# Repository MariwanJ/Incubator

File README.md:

# Incubator Using PID controller - Arduino Nano.

The incubator system is built using an Arduino Nano and a PID controller. The key components include:

- Incubator enclosure
- PID controller for temperature regulation
- Arduino Nano as the main microcontroller
- Egg turner mechanism for gently rotating the eggs during incubation

The egg turner is an essential part of the incubator system, as it helps ensure the eggs develop properly by exposing different areas to the heat and humidity within the incubator. 

Note that the specific 3D printed holder or design for the egg turner is not included, as there are many different options and choices available for this component.

An additional Arduino board is used to control the egg turner mechanism separately from the main incubator controller.

Feel free to modify, improve, and submit pull requests to the GitHub repository for this project.

Additional Notes:

- This incubator project was originally developed in 2020.

- The photos included show an earlier, faulty version of the incubator. These were added to demonstrate the issues that were targeted and fixed in the updated design.

- The design has been further updated to fix other issues and add more footprints, using KICAD 7.0.

Mariwan Jalal 2023-05-13

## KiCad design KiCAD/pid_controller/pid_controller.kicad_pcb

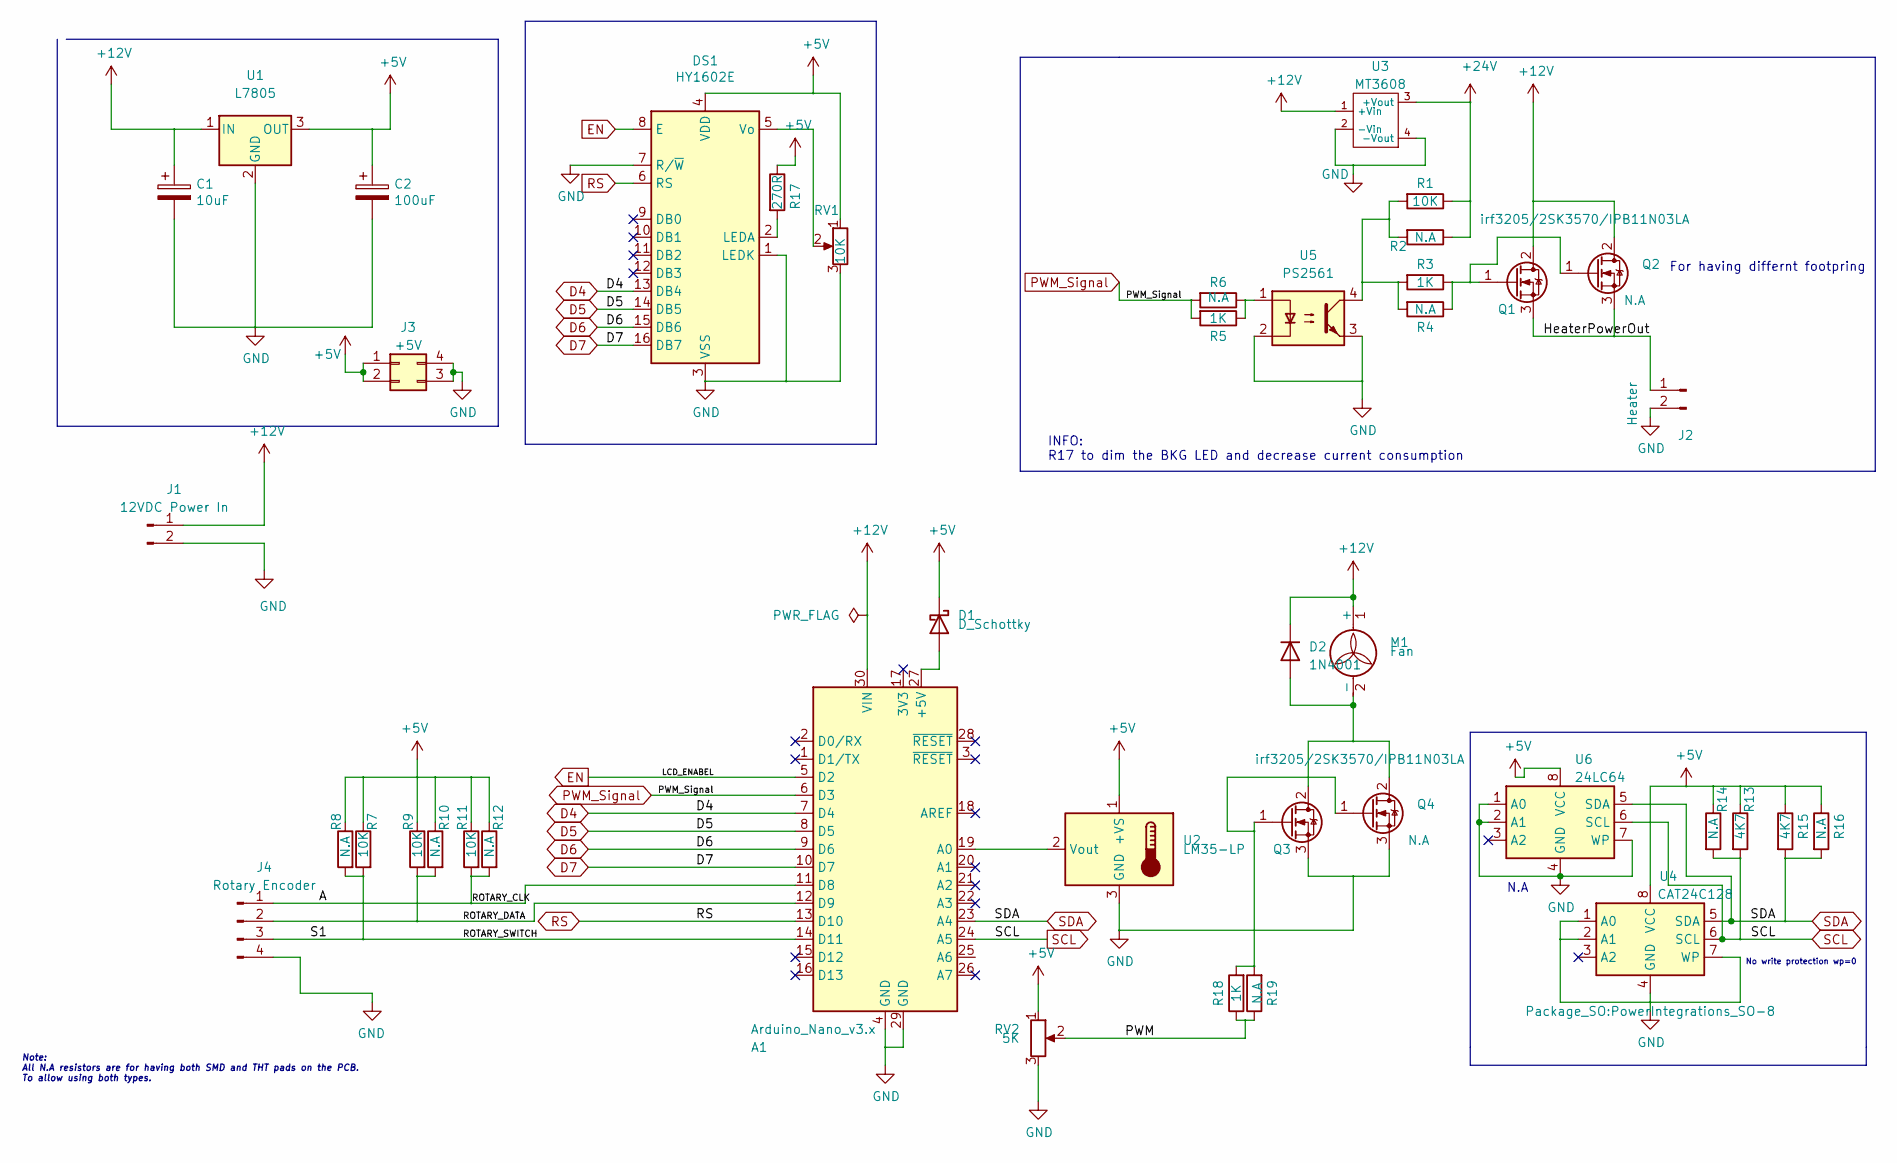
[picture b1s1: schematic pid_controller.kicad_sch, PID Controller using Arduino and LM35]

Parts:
A1: Arduino_Nano_v3.x; Arduino_Nano
C1: 10uF; CP_Radial_D6.3mm_P2.50mm
C2: 100uF; CP_Radial_D6.3mm_P2.50mm
D1: D_Schottky; D_A-405_P5.08mm_Vertical_KathodeUp
D2: 1N4001; D_DO-41_SOD81_P10.16mm_Horizontal
DS1: HY1602E; LCD-016N002L
J1: 12VDC Power In; TerminalBlock_Altech_AK300-2_P5.00mm
J2: Heater; TerminalBlock_Altech_AK300-2_P5.00mm
J3: +5V; PinHeader_2x02_P2.54mm_Vertical
J4: Rotary Encoder; PinHeader_1x04_P2.54mm_Horizontal
M1: Fan; PinHeader_1x02_P2.54mm_Vertical
Q1, Q3: irf3205/2SK3570/IPB11N03LA; TO-220-3_Vertical
Q2, Q4: N.A; TO-263-2
R1, R7, R9, R11: 10K; R_1210_3225Metric
R2, R4, R8, R10, R12, R14, R16: N.A; R_Axial_DIN0309_L9.0mm_D3.2mm_P12.70mm_Horizontal
R3: 1K; R_1210_3225Metric
R5, R18: N.A; R_1210_3225Metric
R6, R19: 1K; R_Axial_DIN0309_L9.0mm_D3.2mm_P12.70mm_Horizontal
R13, R15: 4K7; R_1210_3225Metric
R17: 270R; R_1210_3225Metric
RV1: 10K; Potentiometer_Bourns_3299W_Vertical
RV2: 5K; PinHeader_1x03_P2.54mm_Vertical
U1: L7805; TO-220-3_Vertical
U2: LM35-LP; PinHeader_1x03_P2.54mm_Vertical
U3: MT3608
U4: CAT24C128; PowerIntegrations_SO-8
U5: PS2561; DIP-4_W7.62mm
U6: 24LC64; DIP-8_W10.16mm_LongPads

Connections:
+5V: C2.1, D1.1 (K), DS1.4 (VDD), J3.1, J3.2, R7.1, R8.1, R9.1, R10.1, R11.1, R12.1, R13.1, R14.1, R15.1, R16.1, R17.1, RV1.1, RV2.1, U1.3 (OUT), U2.1 (+VS), U4.8 (VCC), U6.8 (VCC)
+12V: A1.30 (VIN), C1.1, D2.1 (K), J1.1, M1.1 (+), Q1.2 (D), Q2.2 (D), U1.1 (IN), U3.1 (+Vin)
+24V: R1.1, R2.1, U3.3 (+Vout)
/A: A1.11 (D8), J4.1, R11.2, R12.2
/HeaterPowerOut: J2.1, Q1.3 (S), Q2.3 (S)
/PWM: R18.1, R19.1, RV2.2
/ROTARY_DATA: A1.12 (D9), J4.2, R9.2, R10.2
/ROTARY_SWITCH: A1.14 (D11), J4.3, R7.2, R8.2
D4: A1.7 (D4), DS1.13 (DB4)
D5: A1.8 (D5), DS1.14 (DB5)
D6: A1.9 (D6), DS1.15 (DB6)
D7: A1.10 (D7), DS1.16 (DB7)
EN: A1.5 (D2), DS1.8 (E)
GND: A1.4 (GND), A1.29 (GND), C1.2, C2.2, DS1.1 (LEDK), DS1.3 (VSS), DS1.7 (R/~W), J1.2, J2.2, J3.3, J3.4, J4.4, Q3.3 (S), Q4.3 (S), RV1.3, RV2.3, U1.2 (GND), U2.3 (GND), U3.2 (-Vin), U3.4 (-Vout), U4.1 (A0), U4.2 (A1), U4.4 (GND), U4.7 (WP), U5.2, U5.3, U6.1 (A0), U6.2 (A1), U6.4 (GND), U6.7 (WP)
unnamed: A1.27 (+5V), D1.2 (A)
unnamed: A1.19 (A0), U2.2 (Vout)
unnamed: D2.2 (A), M1.2 (-), Q3.2 (D), Q4.2 (D)
unnamed: DS1.2 (LEDA), R17.2
unnamed: DS1.5 (Vo), RV1.2
unnamed: Q1.1 (G), Q2.1 (G), R3.1, R4.1
unnamed: Q3.1 (G), Q4.1 (G), R18.2, R19.2
unnamed: R1.2, R2.2, R3.2, R4.2, U5.4
unnamed: R5.1, R6.1, U5.1
PWM_Signal: A1.6 (D3), R5.2, R6.2
RS: A1.13 (D10), DS1.6 (RS)
SCL: A1.24 (A5), R13.2, R14.2, U4.6 (SCL), U6.6 (SCL)
SDA: A1.23 (A4), R15.2, R16.2, U4.5 (SDA), U6.5 (SDA)

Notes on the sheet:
N.A
No write protection wp=0
INFO: R17 to dim the BKG LED and decrease current consumption
Note: All N.A resistors are for having both SMD and THT pads on the PCB. To allow using both types.
For having differnt footpring

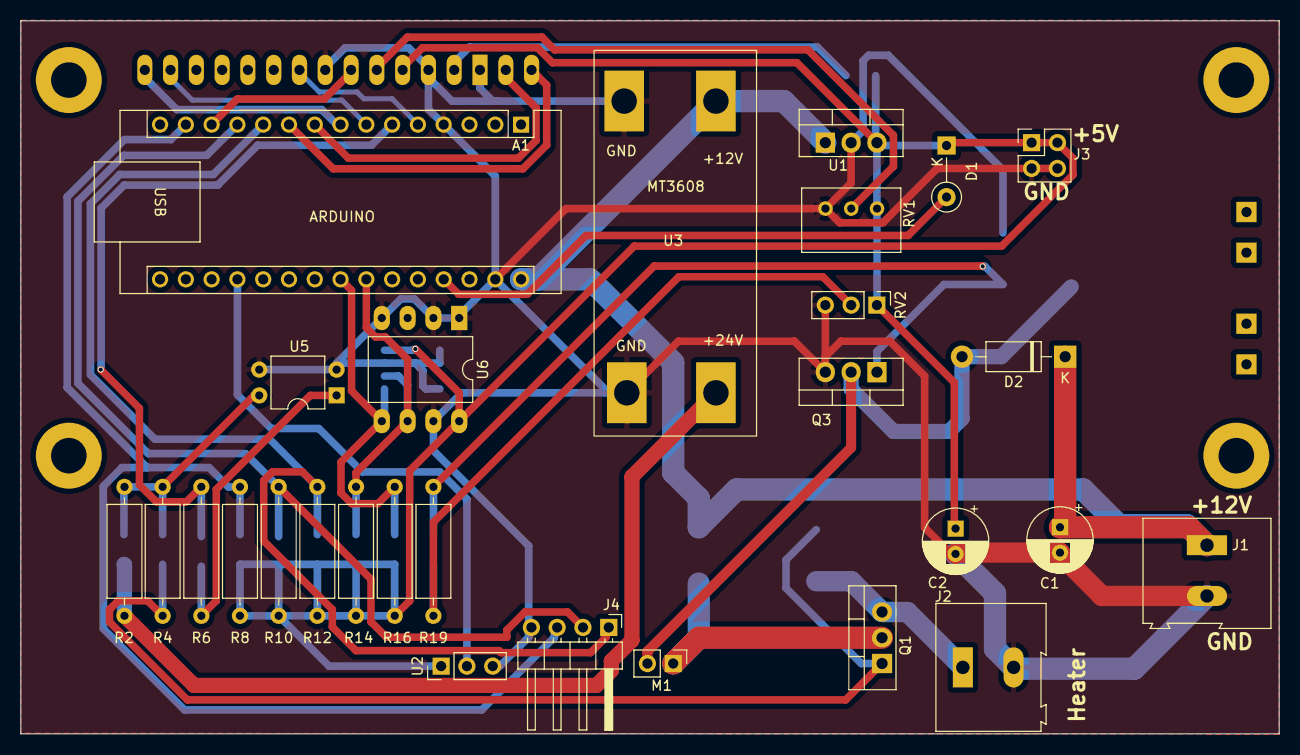
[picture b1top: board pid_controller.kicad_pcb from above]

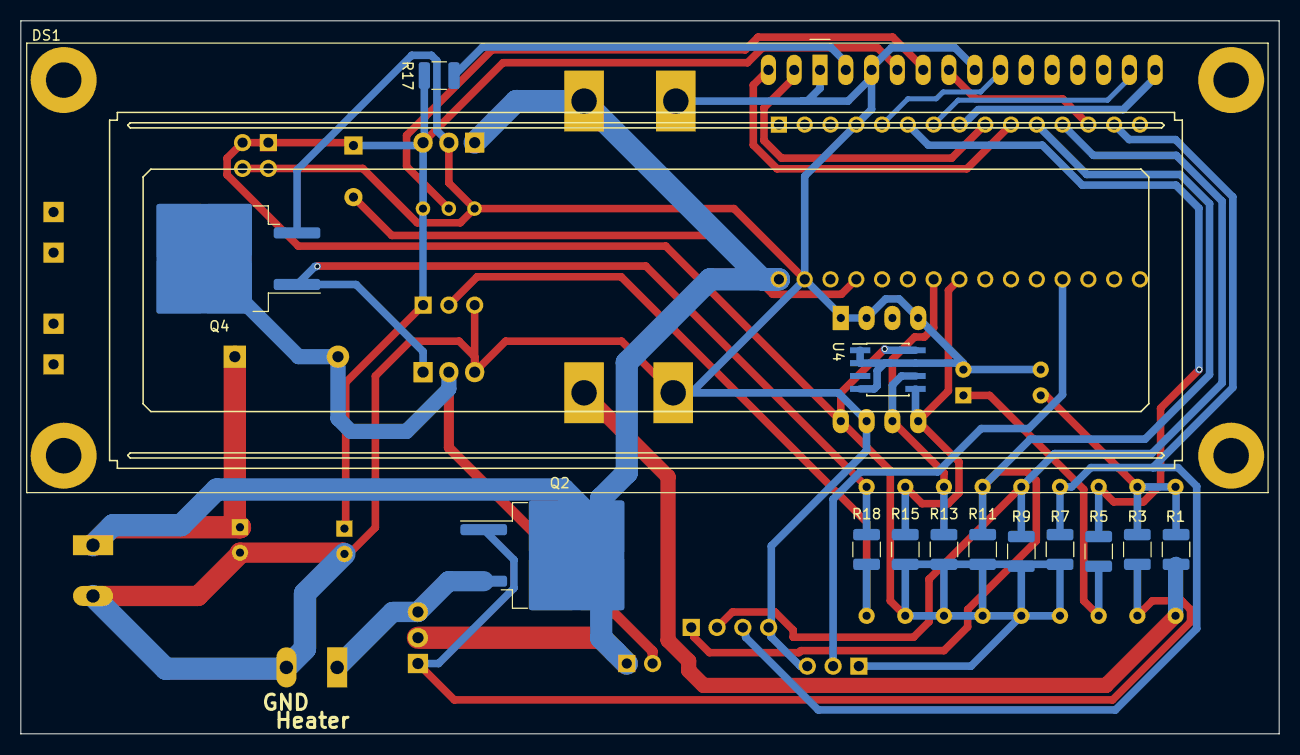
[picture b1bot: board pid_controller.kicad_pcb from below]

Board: 2 copper layers, 124.0 x 70.2 mm, 42 parts (14 on the bottom side), 27 nets.

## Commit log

2022-05-14 adding all parts to the github
2022-05-14 wrong arduino name
2022-05-15 typo fix
2022-05-15 adding production files
2022-06-03 add photo from the faulty PCB & PCBA
2022-06-05 adding more silkscreen info to the PCB
2023-05-13 Redesign the PCB and add some other footprints
2023-05-13 adding topside
2023-08-10 Update PID_temperature_control_parallelLCD.ino
    type fix
2023-08-10 Update PID_temperature_control_parallelLCD.ino
    Typo fix
2025-01-14 Adding rotary encoder library used in the project
    Without the library, you cannot build the project. The library is not mine .. look at http://www.buxtronix.net/2011/10/rotary-encoders-done-properly.html
